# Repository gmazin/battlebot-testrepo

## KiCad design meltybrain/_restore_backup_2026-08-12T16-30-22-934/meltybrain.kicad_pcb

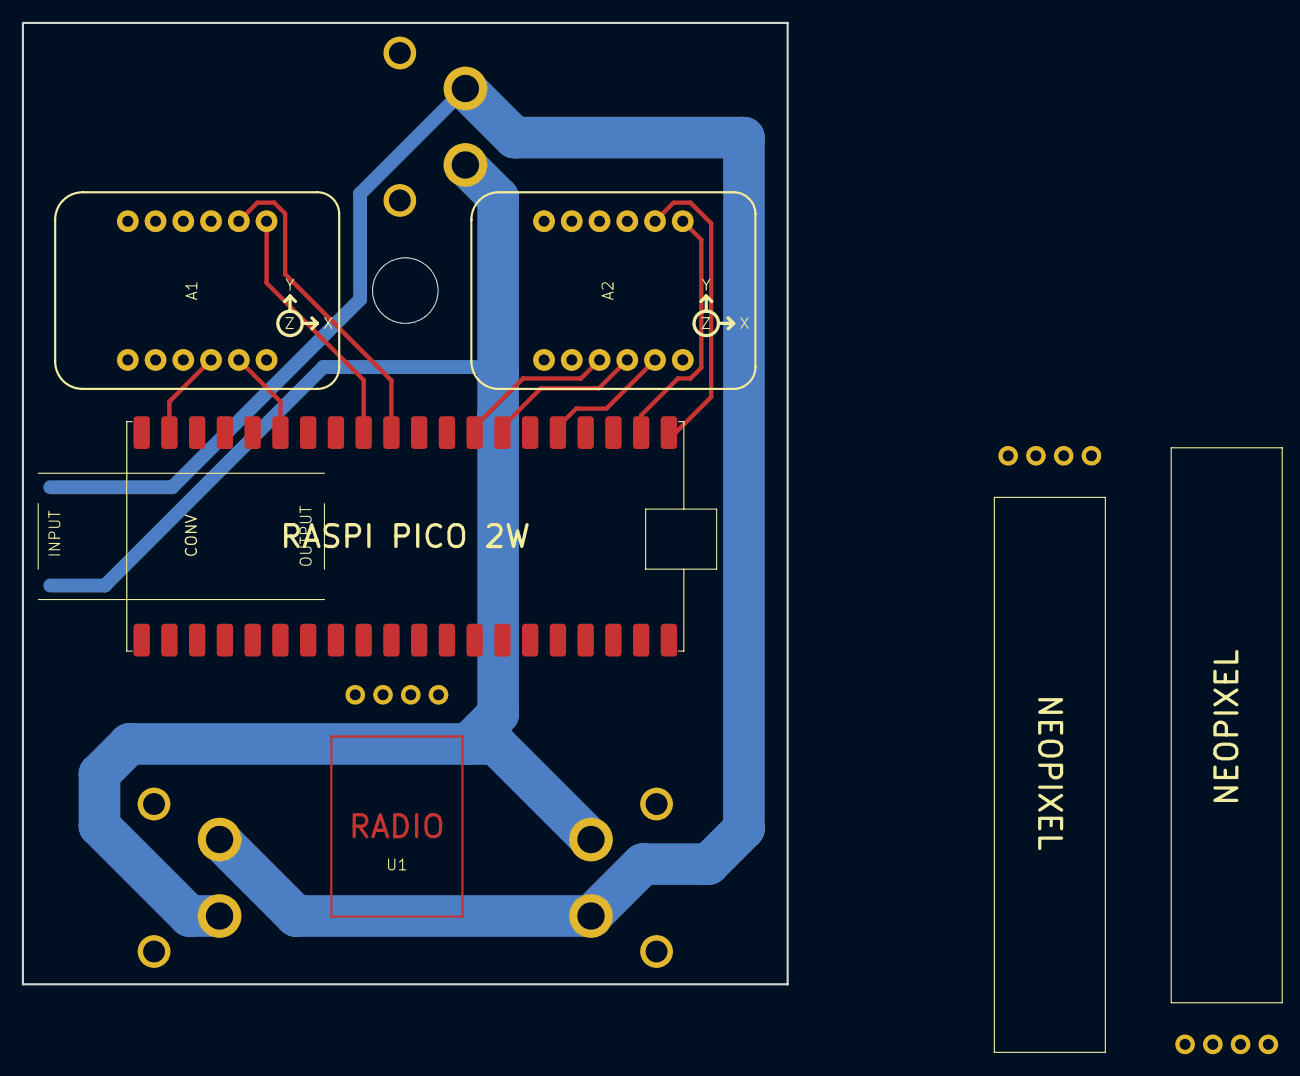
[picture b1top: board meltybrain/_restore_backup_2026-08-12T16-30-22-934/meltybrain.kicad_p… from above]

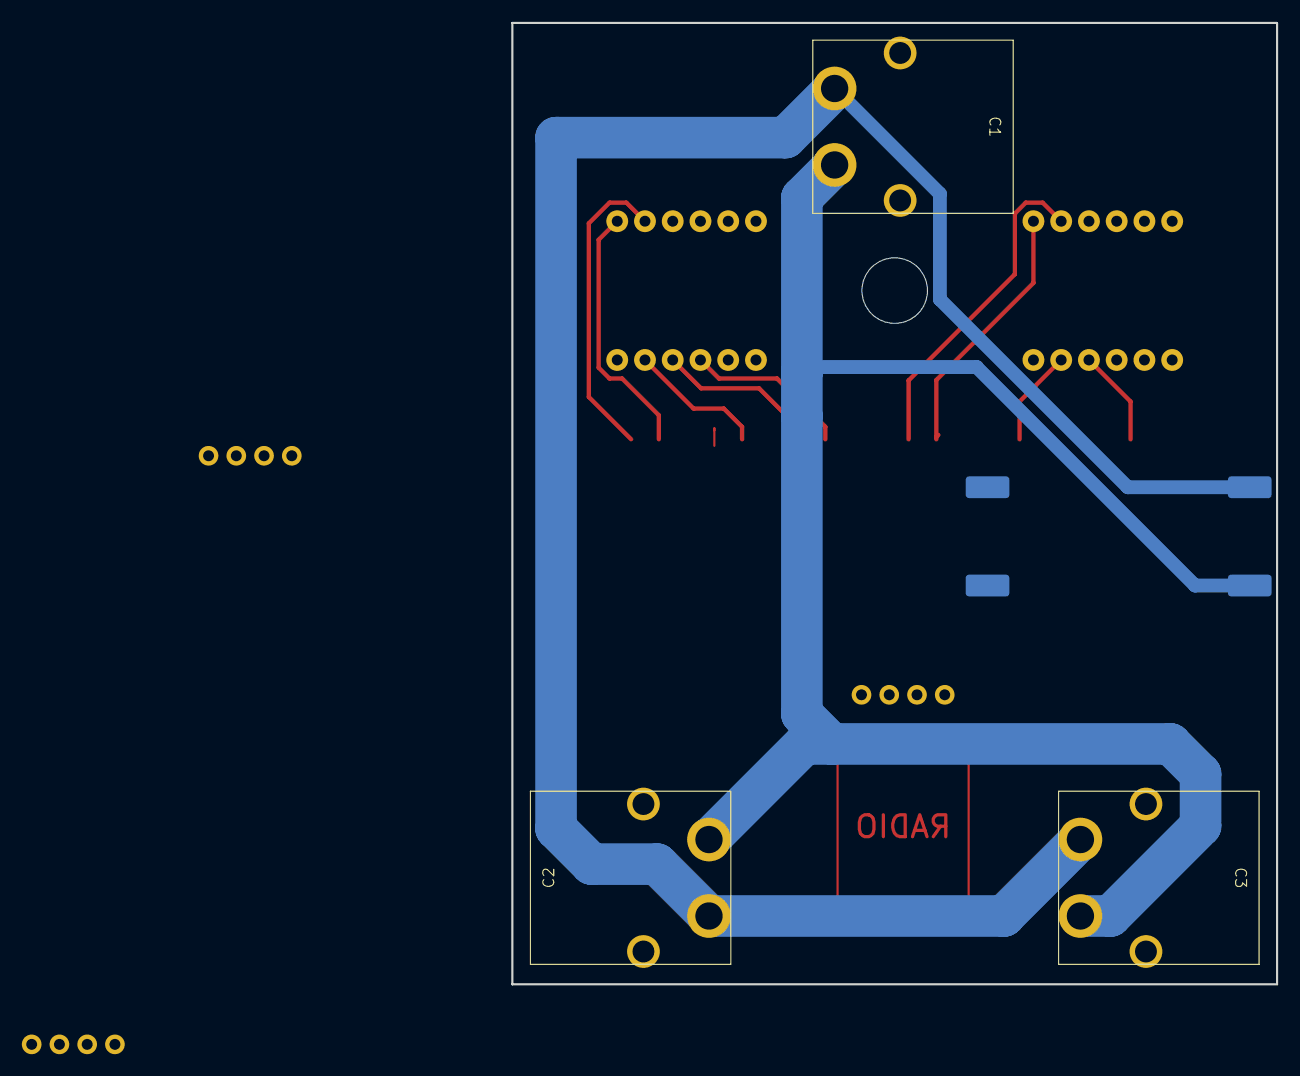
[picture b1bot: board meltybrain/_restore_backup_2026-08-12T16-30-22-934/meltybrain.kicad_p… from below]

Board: 2 copper layers, 70.0 x 88.0 mm, 10 parts (3 on the bottom side), 17 nets.

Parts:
A1, A2: accel
C1, C2, C3: XT60PW_MALE
D1, D2: NeoPixel_8; neopixel
P1: RaspberryPi_Pico_2W; pico2w
U1: receiver
U3: 5v

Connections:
unnamed: A1.1 (5V), A2.1 (5V), D1.3 (5V), D2.3 (5V), P1.39 (VSYS), U1.2 (5V), U3.3 (V_OUT)
unnamed: A1.12 (CS), P1.12 (SPI1_CS)
unnamed: A1.3 (GND3), P1.23 (GND23)
unnamed: A1.4 (SCL), P1.19 (SPI1_CLK)
unnamed: A1.5 (SDA), P1.15 (SPI1_TX)
unnamed: A1.11 (SDO), P1.11 (SPI1_RX)
unnamed: A2.12 (CS), P1.2 (SPI0_CS)
unnamed: A2.3 (GND3), P1.8 (GND8)
unnamed: A2.4 (SCL), P1.7 (SPI0_SCK)
unnamed: A2.5 (SDA), P1.5 (SPI0_TX)
unnamed: A2.11 (SDO), P1.1 (SPI0_RX)
unnamed: C1.1 (GND), C2.1 (GND), C3.1 (GND), U3.2 (GND_IN)
unnamed: C1.2 (VCC), C2.2 (VCC), C3.2 (VCC), U3.1 (V_IN)
unnamed: D1.4 (GND), D2.4 (GND), U1.1 (GND), U3.4 (GND_OUT)
unnamed: P1.13 (GND), P1.18 (GND), P1.28 (GND), P1.38 (GND)
unnamed: P1.22 (UART0_RX), U1.3 (TX)
unnamed: P1.21 (UART0_TX), U1.4 (RX)

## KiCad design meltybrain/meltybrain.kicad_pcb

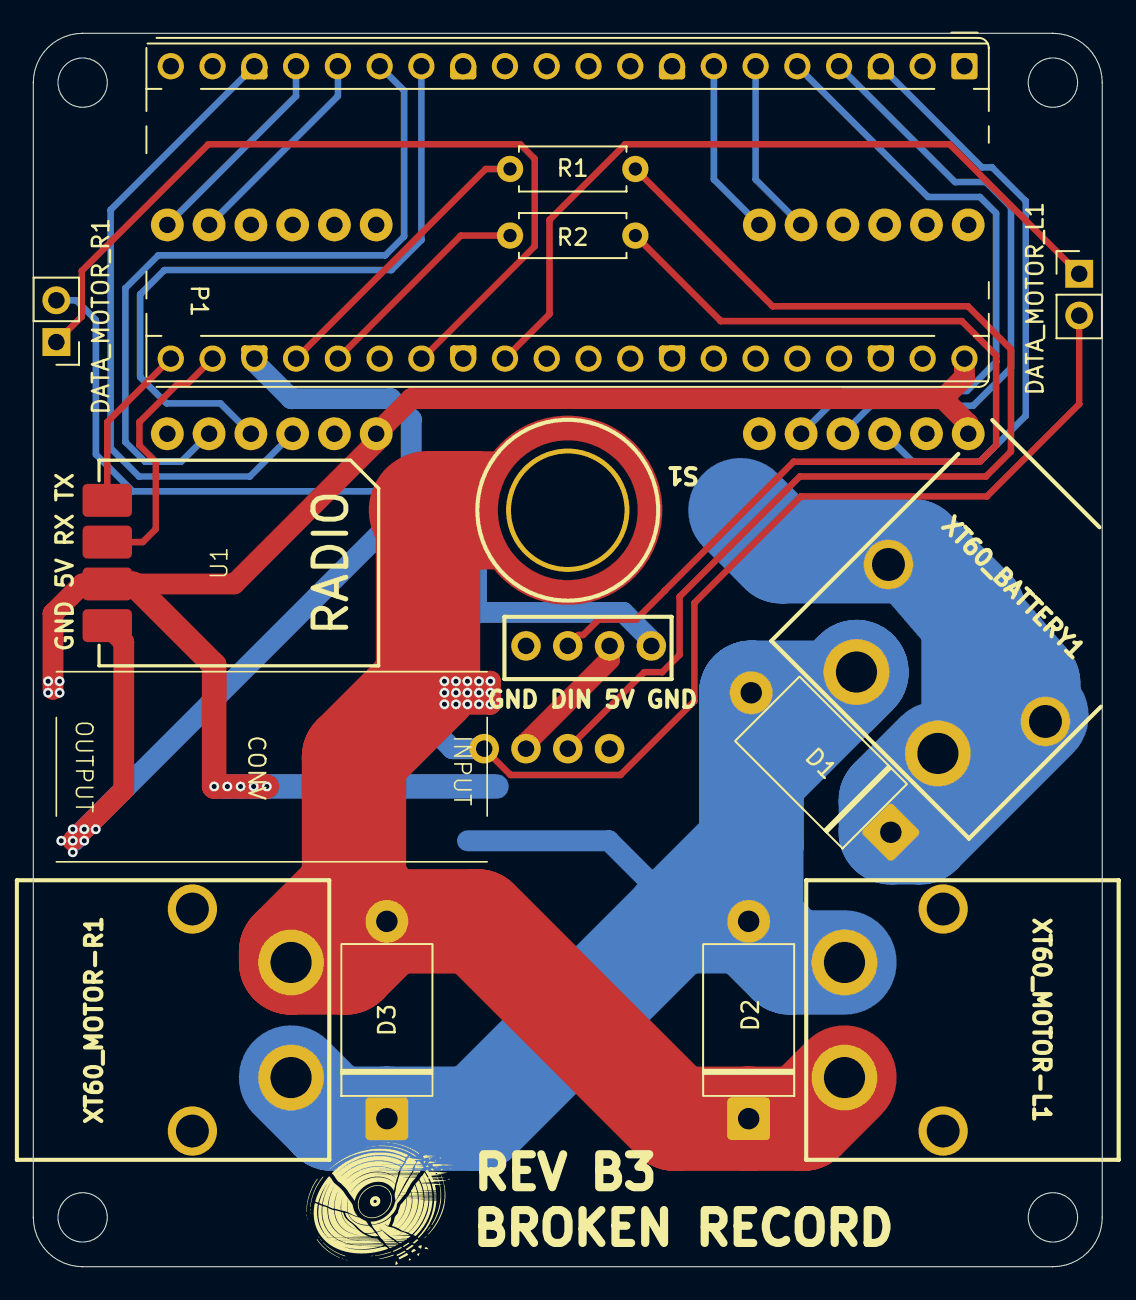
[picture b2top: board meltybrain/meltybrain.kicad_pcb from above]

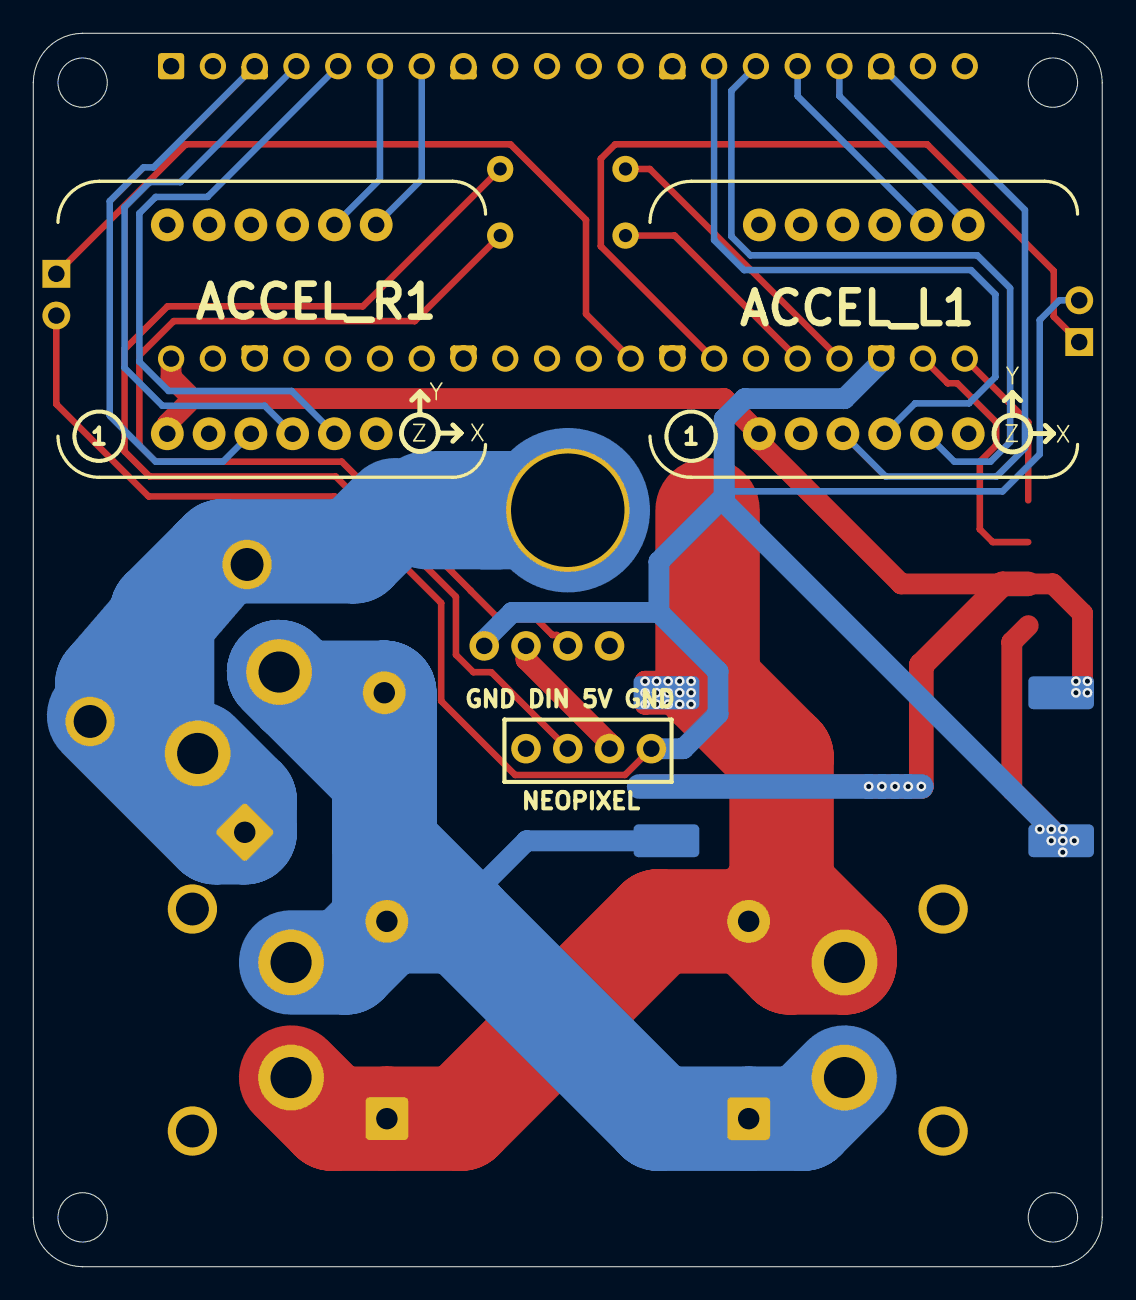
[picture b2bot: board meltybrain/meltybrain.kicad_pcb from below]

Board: 2 copper layers, 65.0 x 75.0 mm, 18 parts (4 on the bottom side), 23 nets.

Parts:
5V_REGULATOR1: 5v
ACCEL_L1: accel
ACCEL_R1: accel
D1: D_Zener; DIODE
D2, D3: D_TVS; DIODE
DATA_MOTOR_L1: PinHeader_1x02_P2.54mm_Vertical
DATA_MOTOR_R1: PinHeader_1x02_P2.54mm_Vertical
LED_BOT1: NeoPixel_8; neopixel
LED_TOP1: NeoPixel_8; neopixel
P1: RaspberryPi_Pico_2W; RaspberryPi_Pico_Common_THT
R1, R2: 470Ω; R_Axial_DIN0207_L6.3mm_D2.5mm_P7.62mm_Horizontal
S1: 10-32_PEM_SWITCH
U1: receiver
XT60_BATTERY1, XT60_MOTOR-L1, XT60_MOTOR-R1: XT60PW_MALE

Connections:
unnamed: 5V_REGULATOR1.2 (GND_IN), D1.2 (A), D2.2 (A2), D3.1 (A1), XT60_BATTERY1.1 (GND), XT60_MOTOR-L1.1 (GND), XT60_MOTOR-R1.1 (GND)
unnamed: 5V_REGULATOR1.4 (GND_OUT), DATA_MOTOR_L1.2 (GND), DATA_MOTOR_R1.2 (GND), LED_BOT1.4 (GND), LED_TOP1.4 (GND), P1.23 (GND), U1.1 (GND)
unnamed: 5V_REGULATOR1.1 (V_IN), D2.1 (A1), D3.2 (A2), S1.1 (IN), XT60_MOTOR-L1.2 (VCC), XT60_MOTOR-R1.2 (VCC)
unnamed: 5V_REGULATOR1.3 (V_OUT), ACCEL_L1.1 (5V), ACCEL_R1.1 (5V), LED_BOT1.3 (5V), LED_TOP1.3 (5V), P1.40 (VBUS), U1.2 (5V)
unnamed: ACCEL_L1.12 (CS), P1.17 (SPI1_CS)
unnamed: ACCEL_L1.3 (GND3), P1.18 (GND)
unnamed: ACCEL_L1.4 (SCL), P1.14 (SPI1_CLK)
unnamed: ACCEL_L1.5 (SDA), P1.15 (SPI1_TX)
unnamed: ACCEL_L1.11 (SDO), P1.16 (SPI1_RX)
unnamed: ACCEL_R1.12 (CS), P1.7 (SPI0_CS)
unnamed: ACCEL_R1.3 (GND3), P1.3 (GND)
unnamed: ACCEL_R1.4 (SCL), P1.4 (SPI0_SCK)
unnamed: ACCEL_R1.5 (SDA), P1.5 (SPI0_TX)
unnamed: ACCEL_R1.11 (SDO), P1.6 (SPI0_RX)
unnamed: D1.1 (K), S1.2 (OUT), XT60_BATTERY1.2 (VCC)
unnamed: DATA_MOTOR_L1.1 (DATA), P1.29 (GP22)
unnamed: DATA_MOTOR_R1.1 (DATA), P1.27 (GPIO21)
unnamed: LED_BOT1.2 (DIN), R2.2
unnamed: LED_TOP1.2 (DIN), R1.2
unnamed: P1.24 (GPIO18), R1.1
unnamed: P1.25 (GPIO19), R2.1
unnamed: P1.22 (UART0_RX), U1.3 (TX)
unnamed: P1.21 (UART0_TX), U1.4 (RX)

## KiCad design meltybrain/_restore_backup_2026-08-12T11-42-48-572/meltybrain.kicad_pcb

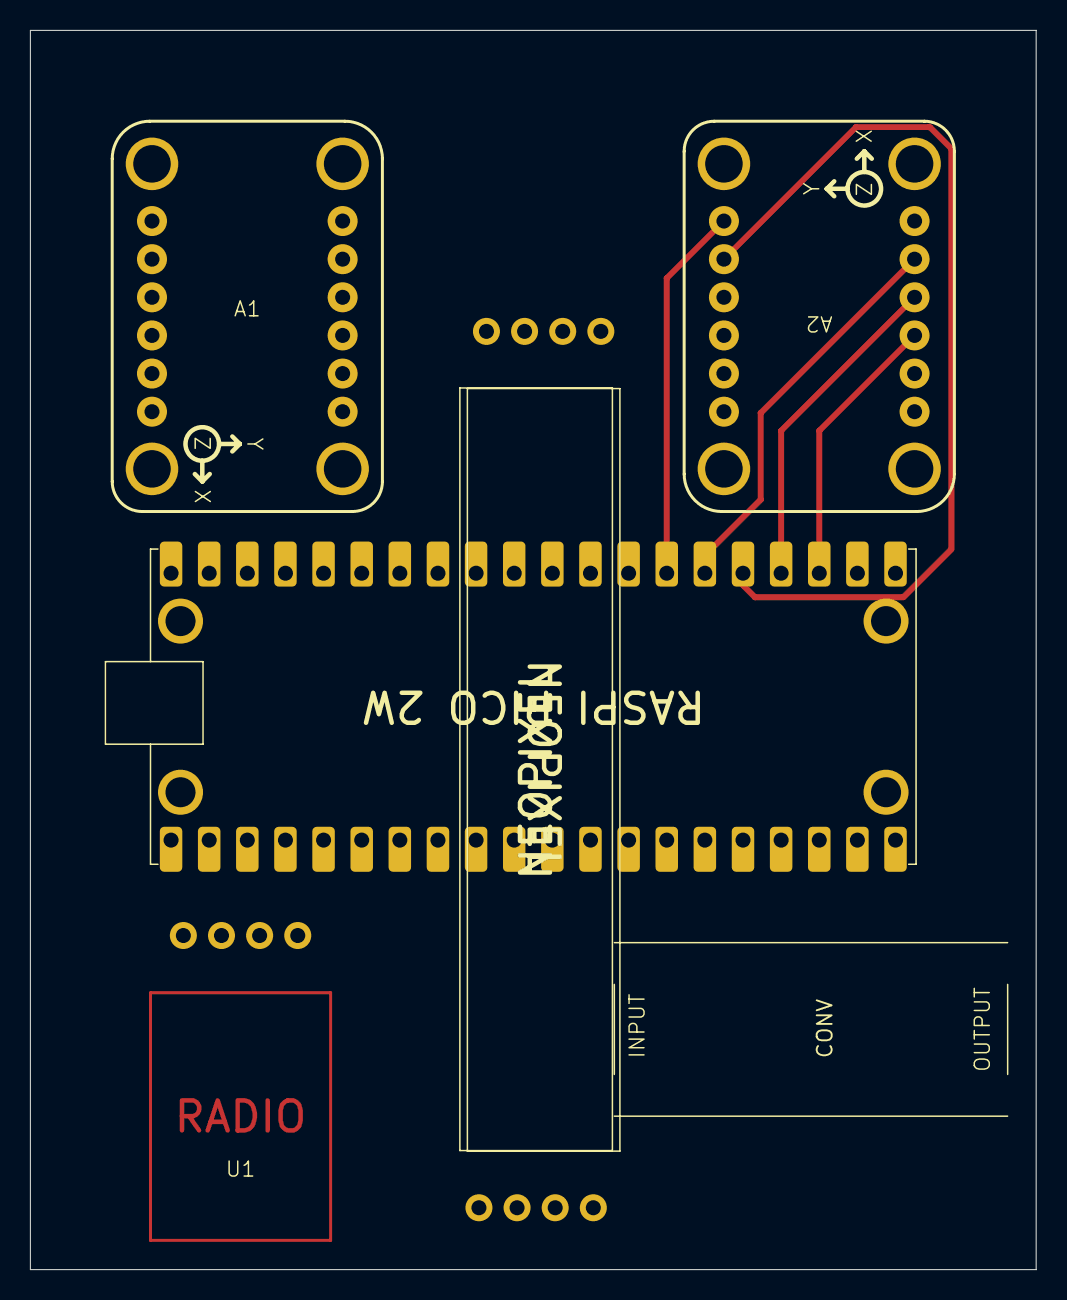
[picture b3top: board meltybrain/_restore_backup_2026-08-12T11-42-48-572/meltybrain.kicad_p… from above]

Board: 2 copper layers, 67.0 x 82.5 mm, 7 parts (0 on the bottom side), 16 nets.

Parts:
A1, A2: accel
D1, D2: NeoPixel_8; neopixel
P1: RaspberryPi_Pico_2W; pico2w
U1: receiver
U3: 5v

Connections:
unnamed: A1.1 (5V), A2.1 (5V), D1.3 (5V), D2.3 (5V), P1.39 (VSYS), U1.1 (GND), U3.3 (V_OUT)
unnamed: A1.12 (CS), P1.17 (GPIO13)
unnamed: A1.4 (SCL), P1.14 (GPIO10)
unnamed: A1.5 (SDA), P1.16 (GPIO12)
unnamed: A1.11 (SDO), P1.15 (GPIO11)
unnamed: A2.12 (CS), P1.27 (GPIO21)
unnamed: A2.3 (GND3), P1.23 (GND23)
unnamed: A2.4 (SCL), P1.24 (GPIO18)
unnamed: A2.5 (SDA), P1.26 (GPIO20)
unnamed: A2.11 (SDO), P1.25 (GPIO19)
unnamed: D1.2 (DIN), P1.4 (GPIO2)
unnamed: D2.2 (DIN), P1.5 (GPIO3)
unnamed: D1.1 (GND), D1.4 (GND), D2.1 (GND), D2.4 (GND)
unnamed: P1.8 (GND), P1.13 (GND), P1.18 (GND), P1.28 (GND), P1.38 (GND)
unnamed: P1.1 (GPIO0), U1.4 (RX)
unnamed: P1.2 (GPIO1), U1.3 (TX)
